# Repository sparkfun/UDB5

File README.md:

UDB5 - UAV Development Board
===============

[  
*UDB5 (GPS-11703)*](https://www.sparkfun.com/products/11703)

The UDB5 is the fith generation UAV Development board. The main difference from UDB4 is that we moved to an MPU-6000 for the accelerometer and gyro.

For information on the codebase see the [gentlenav repository](https://code.google.com/p/gentlenav/) on google code. 

Repository Contents
-------------------

* **/hardware** - Eagle PCB layout files

License Information
-------------------

All contents of this repository are released under [Creative Commons Share-alike 3.0](http://creativecommons.org/licenses/by-sa/3.0/).

Authors: Jordan McConnell, Aaron Weiss @ SparkFun Electonics

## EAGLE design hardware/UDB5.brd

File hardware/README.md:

UDB5
====

These are the Eagle CAD files for the UDB5.

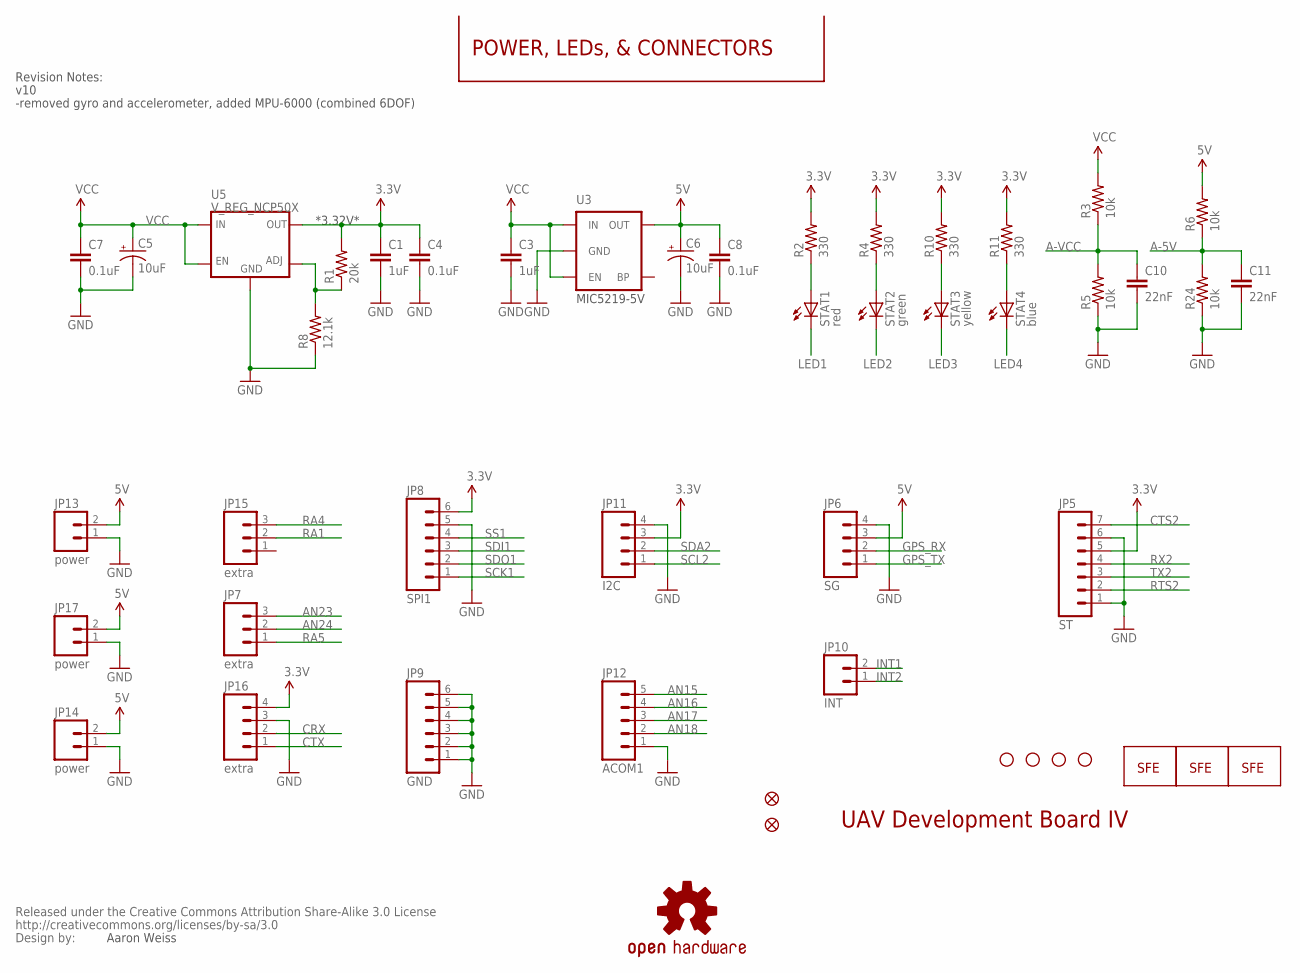
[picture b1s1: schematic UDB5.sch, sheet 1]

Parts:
C1, C3: 1uF; 0402-CAP
C4, C7, C8: 0.1uF; 0402-CAP
C5, C6: 10uF; EIA3216
C10, C11: 22nF; 0402-CAP
CC_TEXT1: CREATIVE_COMMONS
JP3: LOGO-SFENEW; SFE-NEW-WEBLOGO
JP5: ST; 1X07
JP6: SG; 1X04
JP7, JP15: extra; 1X03
JP8: SPI1; 1X06
JP9: GND; 1X06
JP10: INT; 1X02
JP11: I2C; 1X04
JP12: ACOM1; 1X05
JP13, JP14, JP17: power; 1X02
JP16: extra; 1X04
JP18, JP19: FIDUCIAL1X2.5; FIDUCIAL-1X2.5
LOGO1: LOGO-SFENW2; SFE-NEW-WEB
R1: 20k; 0402-RES
R2, R4, R10, R11: 330; 0402-RES
R3, R5, R6, R24: 10k; 0402-RES
R8: 12.1k; 0402-RES
STAT1: red; LED-0603
STAT2: green; LED-0603
STAT3: yellow; LED-0603
STAT4: blue; LED-0603
U3: V_REG_LDOSMD; SOT23-5
U5: V_REG_NCP50X; DPAK-5
U$2, U$3, U$4, U$5: STAND-OFF
U$9: OSHW-LOGOS; OSHW-LOGO-S
U$10: LOGO-SFESK; SFE-LOGO-FLAME

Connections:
3.3V: C1.1, C4.1, JP5.5, JP8.6, JP11.3, JP16.4, R1.2, R2.2, R4.2, R10.2, R11.2, U5.VOUT (OUT); also elsewhere on the board
5V: C6.A (+), C8.1, JP6.3, JP13.2, JP14.2, JP17.2, R6.2, U3.5 (OUT); also elsewhere on the board
A-5V: C11.1, R6.1, R24.2; also elsewhere on the board
A-VCC: C10.1, R3.1, R5.2; also elsewhere on the board
AN15: JP12.5; also elsewhere on the board
AN16: JP12.4; also elsewhere on the board
AN17: JP12.3; also elsewhere on the board
AN18: JP12.2; also elsewhere on the board
AN23: JP7.3; also elsewhere on the board
AN24: JP7.2; also elsewhere on the board
CRX: JP16.2; also elsewhere on the board
CTS2: JP5.7; also elsewhere on the board
CTX: JP16.1; also elsewhere on the board
GND: C1.2, C3.2, C4.2, C5.C (-), C6.C (-), C7.2, C8.2, C10.2, C11.2, JP5.1, JP5.6, JP6.4, JP8.5, JP9.1, JP9.2, JP9.3, JP9.4, JP9.5, JP9.6, JP11.4, JP12.1, JP13.1, JP14.1, JP16.3, JP17.1, R5.1, R8.1, R24.1, U3.2 (GND), U5.GND; also elsewhere on the board
GPS_RX: JP6.2; also elsewhere on the board
GPS_TX: JP6.1; also elsewhere on the board
INT1: JP10.2; also elsewhere on the board
INT2: JP10.1; also elsewhere on the board
LED1: STAT1.C; also elsewhere on the board
LED2: STAT2.C; also elsewhere on the board
LED3: STAT3.C; also elsewhere on the board
LED4: STAT4.C; also elsewhere on the board
unnamed: R2.1, STAT1.A
unnamed: R4.1, STAT2.A
unnamed: R1.1, R8.2, U5.ADJ
unnamed: R10.1, STAT3.A
unnamed: R11.1, STAT4.A
RA1: JP15.2; also elsewhere on the board
RA4: JP15.3; also elsewhere on the board
RA5: JP7.1; also elsewhere on the board
RTS2: JP5.2; also elsewhere on the board
RX2: JP5.4; also elsewhere on the board
SCK1: JP8.1; also elsewhere on the board
SCL2: JP11.1; also elsewhere on the board
SDA2: JP11.2; also elsewhere on the board
SDI1: JP8.3; also elsewhere on the board
SDO1: JP8.2; also elsewhere on the board
SS1: JP8.4; also elsewhere on the board
TX2: JP5.3; also elsewhere on the board
VCC: C3.1, C5.A (+), C7.1, R3.2, U3.1 (IN), U3.3 (EN), U5.EN, U5.VIN (IN); also elsewhere on the board

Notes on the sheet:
Aaron Weiss
POWER, LEDs, & CONNECTORS
UAV Development Board IV
*3.32V*
MIC5219-5V
v10
-removed gyro and accelerometer, added MPU-6000 (combined 6DOF)
Revision Notes:

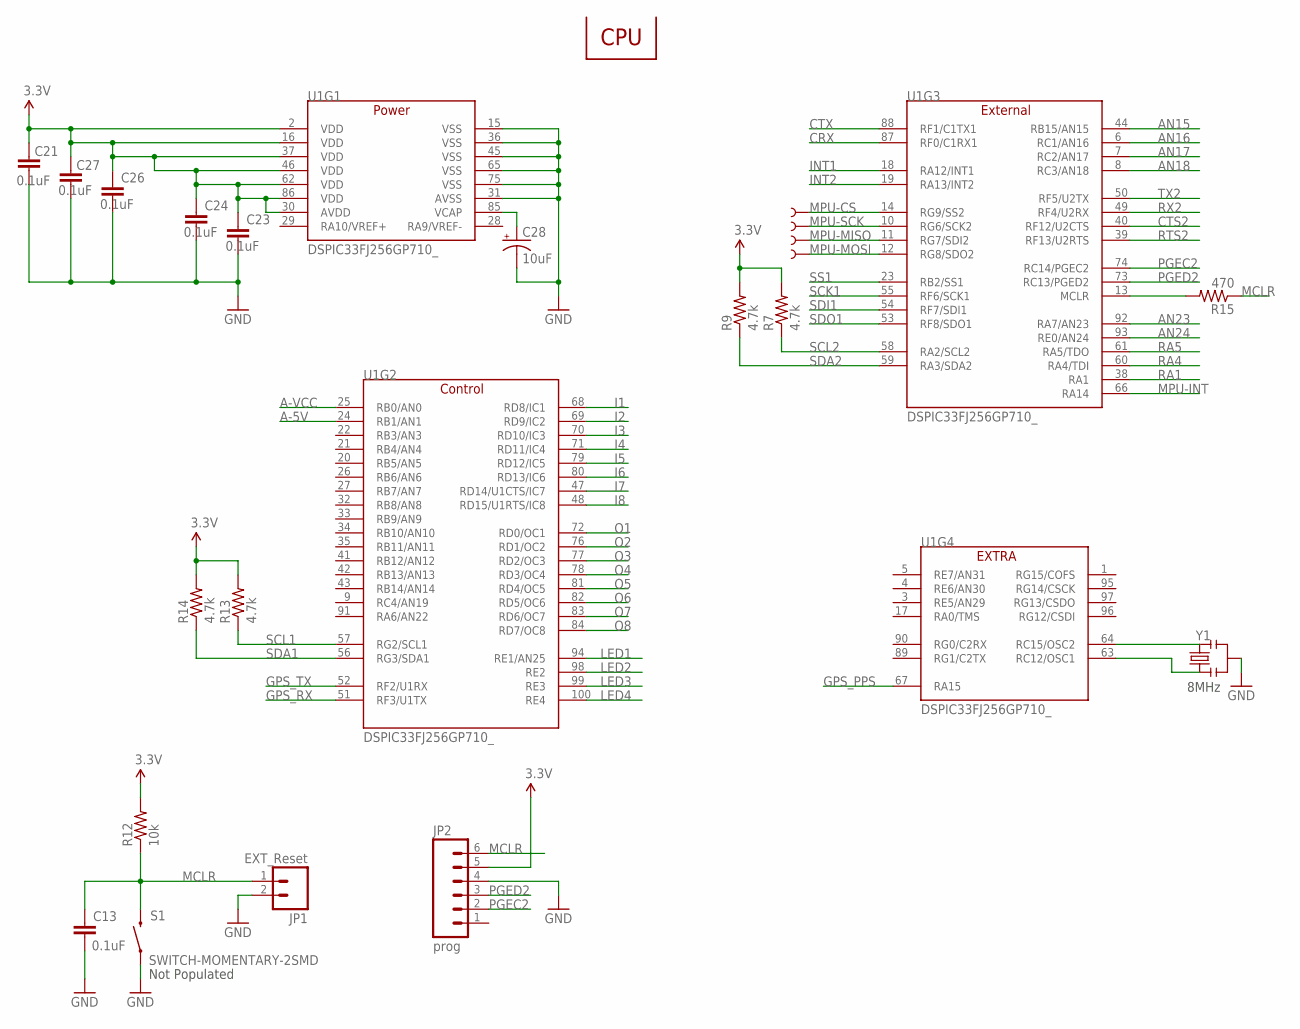
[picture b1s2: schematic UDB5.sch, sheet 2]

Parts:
C13, C21, C23, C24, C26, C27: 0.1uF; 0402-CAP
C28: 10uF; EIA3216
JP1: EXT_Reset; 1X02
JP2: prog; 1X06
R7, R9, R13, R14: 4.7k; 0402-RES
R12: 10k; 0402-RES
R15: 470; 0402-RES
S1: SWITCH-MOMENTARY-2SMD; TACTILE_SWITCH_SMD
TP1, TP2, TP3, TP4: TEST-POINT3; PAD.03X.03
U1: DSPIC33FJ256GP710_; TQFP-100-12X12MM
Y1: RESONATORSMD; RESONATOR-SMD

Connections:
3.3V: C21.1, C23.1, C24.1, C26.1, C27.1, JP2.5, R7.2, R9.2, R12.2, R13.2, R14.2, U1.2 (VDD), U1.16 (VDD), U1.30 (AVDD), U1.37 (VDD), U1.46 (VDD), U1.62 (VDD), U1.86 (VDD); also elsewhere on the board
A-5V: U1.24 (RB1/AN1); also elsewhere on the board
A-VCC: U1.25 (RB0/AN0); also elsewhere on the board
AN15: U1.44 (RB15/AN15); also elsewhere on the board
AN16: U1.6 (RC1/AN16); also elsewhere on the board
AN17: U1.7 (RC2/AN17); also elsewhere on the board
AN18: U1.8 (RC3/AN18); also elsewhere on the board
AN23: U1.92 (RA7/AN23); also elsewhere on the board
AN24: U1.93 (RE0/AN24); also elsewhere on the board
CRX: U1.87 (RF0/C1RX1); also elsewhere on the board
CTS2: U1.40 (RF12/U2CTS); also elsewhere on the board
CTX: U1.88 (RF1/C1TX1); also elsewhere on the board
GND: C13.2, C21.2, C23.2, C24.2, C26.2, C27.2, C28.C (-), JP1.2, JP2.4, S1.1, U1.15 (VSS), U1.31 (AVSS), U1.36 (VSS), U1.45 (VSS), U1.65 (VSS), U1.75 (VSS), Y1.2; also elsewhere on the board
GPS_PPS: U1.67 (RA15); also elsewhere on the board
GPS_RX: U1.51 (RF3/U1TX); also elsewhere on the board
GPS_TX: U1.52 (RF2/U1RX); also elsewhere on the board
I1: U1.68 (RD8/IC1); also elsewhere on the board
I2: U1.69 (RD9/IC2); also elsewhere on the board
I3: U1.70 (RD10/IC3); also elsewhere on the board
I4: U1.71 (RD11/IC4); also elsewhere on the board
I5: U1.79 (RD12/IC5); also elsewhere on the board
I6: U1.80 (RD13/IC6); also elsewhere on the board
I7: U1.47 (RD14/U1CTS/IC7); also elsewhere on the board
I8: U1.48 (RD15/U1RTS/IC8); also elsewhere on the board
INT1: U1.18 (RA12/INT1); also elsewhere on the board
INT2: U1.19 (RA13/INT2); also elsewhere on the board
LED1: U1.94 (RE1/AN25); also elsewhere on the board
LED2: U1.98 (RE2); also elsewhere on the board
LED3: U1.99 (RE3); also elsewhere on the board
LED4: U1.100 (RE4); also elsewhere on the board
MCLR: C13.1, JP1.1, JP2.6, R12.1, R15.1, S1.3 (2)
MPU-CS: TP1.P$1, U1.14 (RG9/SS2); also elsewhere on the board
MPU-INT: U1.66 (RA14); also elsewhere on the board
MPU-MISO: TP3.P$1, U1.11 (RG7/SDI2); also elsewhere on the board
MPU-MOSI: TP4.P$1, U1.12 (RG8/SDO2); also elsewhere on the board
MPU-SCK: TP2.P$1, U1.10 (RG6/SCK2); also elsewhere on the board
unnamed: U1.64 (RC15/OSC2), Y1.3
unnamed: U1.63 (RC12/OSC1), Y1.1
unnamed: R15.2, U1.13 (MCLR)
unnamed: C28.A (+), U1.85 (VCAP)
O1: U1.72 (RD0/OC1); also elsewhere on the board
O2: U1.76 (RD1/OC2); also elsewhere on the board
O3: U1.77 (RD2/OC3); also elsewhere on the board
O4: U1.78 (RD3/OC4); also elsewhere on the board
O5: U1.81 (RD4/OC5); also elsewhere on the board
O6: U1.82 (RD5/OC6); also elsewhere on the board
O7: U1.83 (RD6/OC7); also elsewhere on the board
O8: U1.84 (RD7/OC8); also elsewhere on the board
PGEC2: JP2.2, U1.74 (RC14/PGEC2)
PGED2: JP2.3, U1.73 (RC13/PGED2)
RA1: U1.38 (RA1); also elsewhere on the board
RA4: U1.60 (RA4/TDI); also elsewhere on the board
RA5: U1.61 (RA5/TDO); also elsewhere on the board
RTS2: U1.39 (RF13/U2RTS); also elsewhere on the board
RX2: U1.49 (RF4/U2RX); also elsewhere on the board
SCK1: U1.55 (RF6/SCK1); also elsewhere on the board
SCL1: R13.1, U1.57 (RG2/SCL1); also elsewhere on the board
SCL2: R7.1, U1.58 (RA2/SCL2); also elsewhere on the board
SDA1: R14.1, U1.56 (RG3/SDA1); also elsewhere on the board
SDA2: R9.1, U1.59 (RA3/SDA2); also elsewhere on the board
SDI1: U1.54 (RF7/SDI1); also elsewhere on the board
SDO1: U1.53 (RF8/SDO1); also elsewhere on the board
SS1: U1.23 (RB2/SS1); also elsewhere on the board
TX2: U1.50 (RF5/U2TX); also elsewhere on the board

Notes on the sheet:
CPU
8MHz
Not Populated

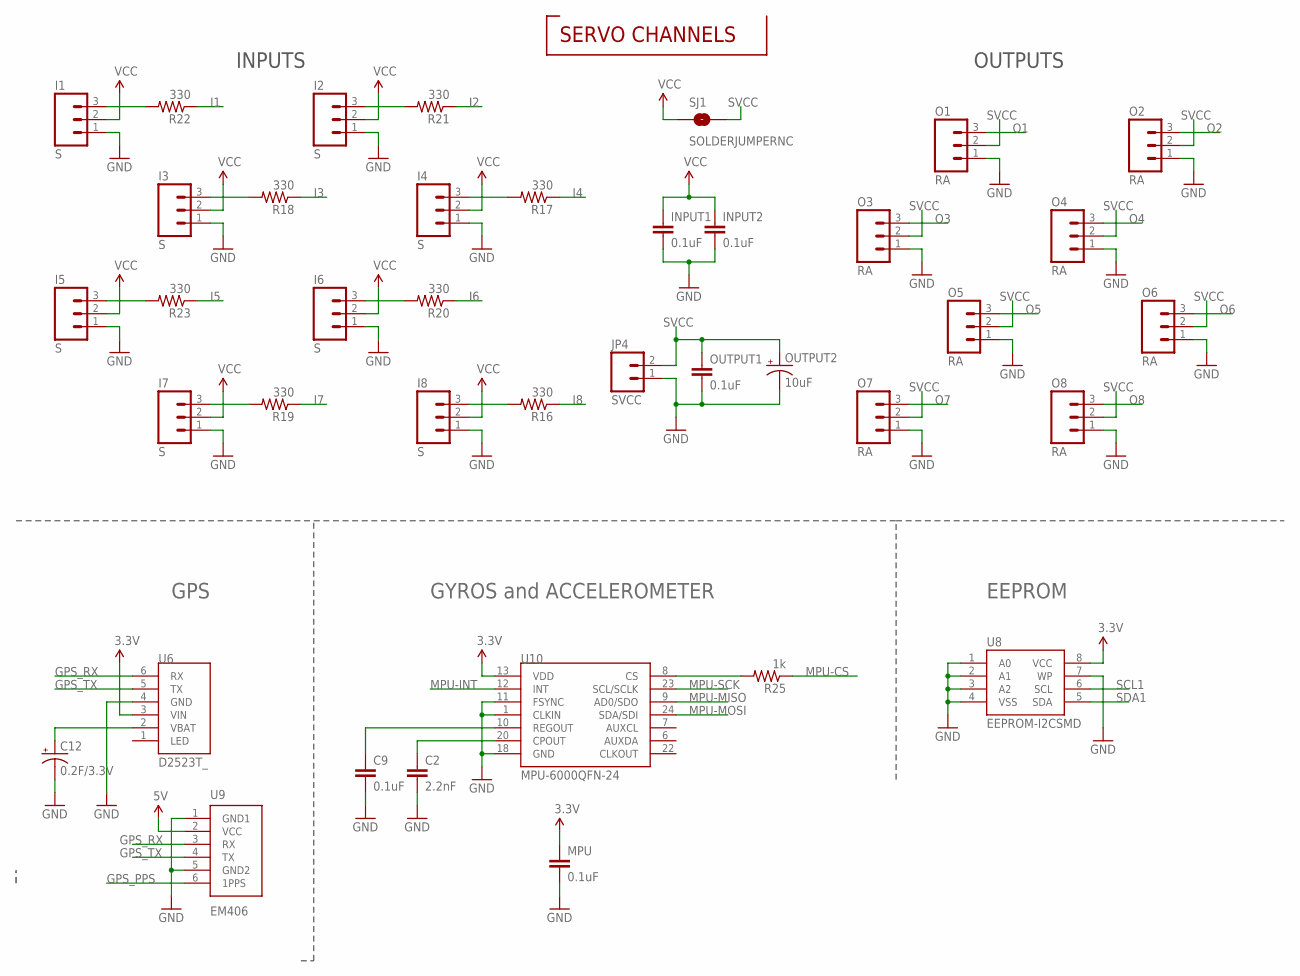
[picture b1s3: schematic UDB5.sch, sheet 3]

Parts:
C2: 2.2nF; 0402-CAP
C9: 0.1uF; 0402-CAP
C12: 0.2F/3.3V; EN_J2
I1, I2, I3, I4, I5, I6, I7, I8: S; 1X03
INPUT1, INPUT2: 0.1uF; 0402-CAP
JP4: SVCC; 1X02
MPU: 0.1uF; 0402-CAP
O1, O2, O3, O4, O5, O6, O7, O8: RA; 1X03
OUTPUT1: 0.1uF; 0402-CAP
OUTPUT2: 10uF; EIA3216
R16, R17, R18, R19, R20, R21, R22, R23: 330; 0402-RES
R25: 1k; 0402-RES
SJ1: SOLDERJUMPERNC; SJ_2S
U6: D2523T_; EM406
U8: EEPROM-I2CSMD; SO08
U9: EM406
U10: MPU-6000QFN-24; QFN-24-TESTING

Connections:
3.3V: MPU.1, U6.3 (VIN), U8.8 (VCC), U10.13 (VDD); also elsewhere on the board
5V: U9.2 (VCC); also elsewhere on the board
GND: C2.2, C9.2, C12.-, I1.1, I2.1, I3.1, I4.1, I5.1, I6.1, I7.1, I8.1, INPUT1.2, INPUT2.2, JP4.1, MPU.2, O1.1, O2.1, O3.1, O4.1, O5.1, O6.1, O7.1, O8.1, OUTPUT1.2, OUTPUT2.C (-), U6.4 (GND), U8.1 (A0), U8.2 (A1), U8.3 (A2), U8.4 (VSS), U8.7 (WP), U9.1 (GND1), U9.5 (GND2), U10.1 (CLKIN), U10.11 (FSYNC), U10.18 (GND); also elsewhere on the board
GPS_PPS: U9.6 (1PPS); also elsewhere on the board
GPS_RX: U6.6 (RX), U9.3 (RX); also elsewhere on the board
GPS_TX: U6.5 (TX), U9.4 (TX); also elsewhere on the board
I1: R22.1; also elsewhere on the board
I2: R21.1; also elsewhere on the board
I3: R18.1; also elsewhere on the board
I4: R17.1; also elsewhere on the board
I5: R23.1; also elsewhere on the board
I6: R20.1; also elsewhere on the board
I7: R19.1; also elsewhere on the board
I8: R16.1; also elsewhere on the board
MPU-CS: R25.1; also elsewhere on the board
MPU-INT: U10.12 (INT); also elsewhere on the board
MPU-MISO: U10.9 (AD0/SDO); also elsewhere on the board
MPU-MOSI: U10.24 (SDA/SDI); also elsewhere on the board
MPU-SCK: U10.23 (SCL/SCLK); also elsewhere on the board
unnamed: C12.+, U6.2 (VBAT)
unnamed: R25.2, U10.8 (CS)
unnamed: C2.1, U10.20 (CPOUT)
unnamed: I8.3, R16.2
unnamed: I4.3, R17.2
unnamed: C9.1, U10.10 (REGOUT)
unnamed: I3.3, R18.2
unnamed: I7.3, R19.2
unnamed: I6.3, R20.2
unnamed: I2.3, R21.2
unnamed: I1.3, R22.2
unnamed: I5.3, R23.2
O1: O1.3; also elsewhere on the board
O2: O2.3; also elsewhere on the board
O3: O3.3; also elsewhere on the board
O4: O4.3; also elsewhere on the board
O5: O5.3; also elsewhere on the board
O6: O6.3; also elsewhere on the board
O7: O7.3; also elsewhere on the board
O8: O8.3; also elsewhere on the board
SCL1: U8.6 (SCL); also elsewhere on the board
SDA1: U8.5 (SDA); also elsewhere on the board
SVCC: JP4.2, O1.2, O2.2, O3.2, O4.2, O5.2, O6.2, O7.2, O8.2, OUTPUT1.1, OUTPUT2.A (+), SJ1.2
VCC: I1.2, I2.2, I3.2, I4.2, I5.2, I6.2, I7.2, I8.2, INPUT1.1, INPUT2.1, SJ1.1; also elsewhere on the board

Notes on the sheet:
INPUTS
OUTPUTS
SERVO CHANNELS
GPS
EEPROM
GYROS and ACCELEROMETER

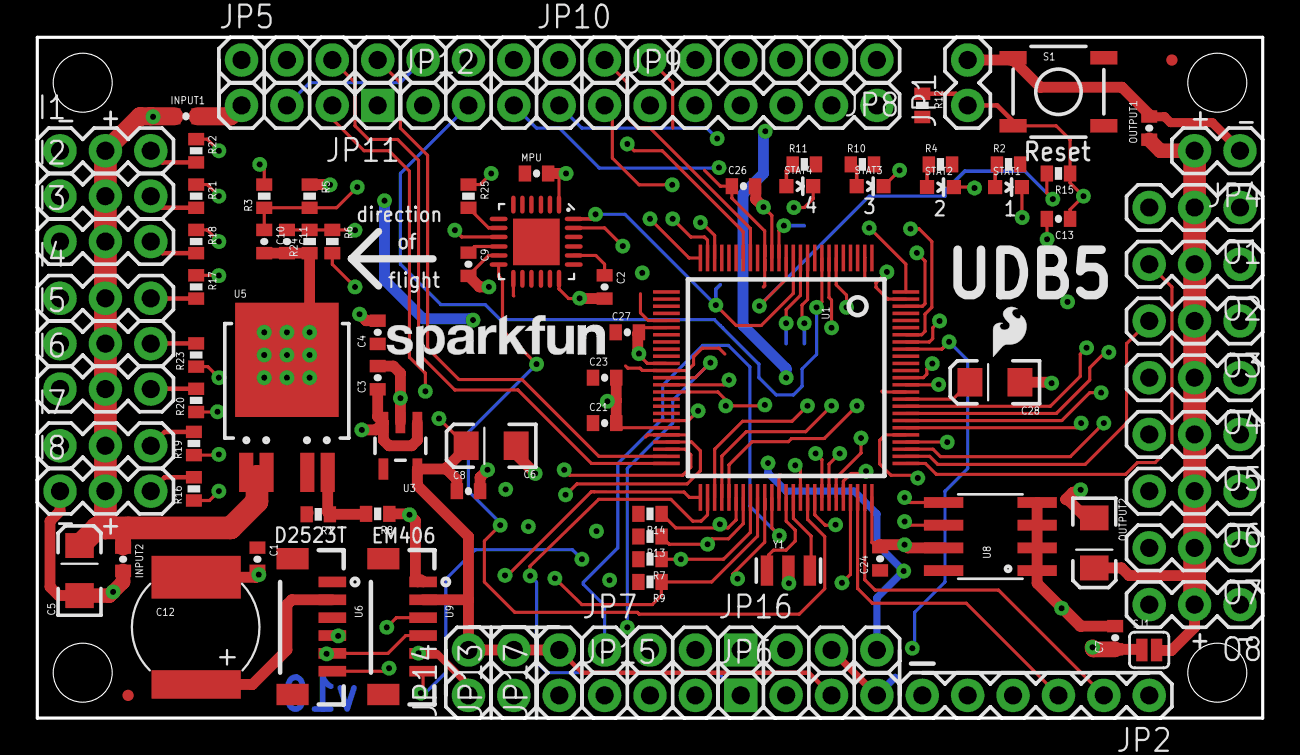
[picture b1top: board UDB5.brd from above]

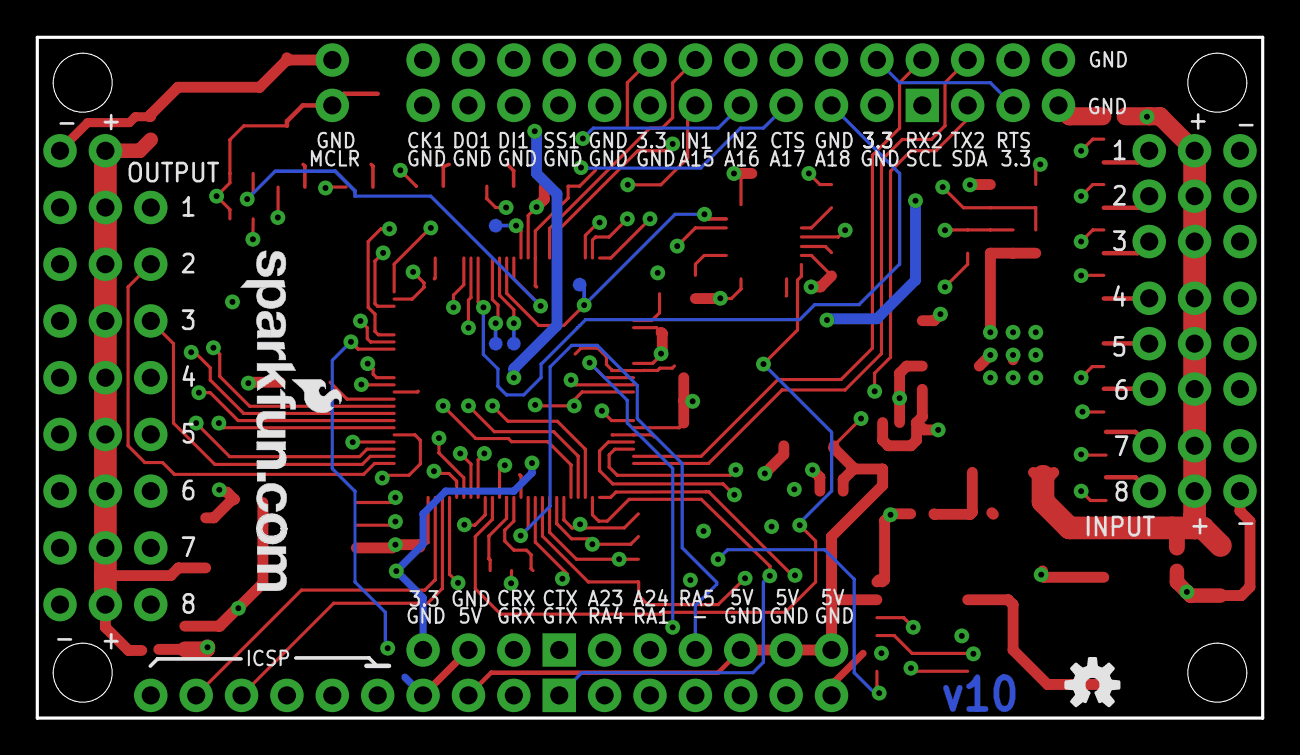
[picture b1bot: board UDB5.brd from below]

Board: 4 copper layers, 68.6 x 38.1 mm, 110 parts (6 on the bottom side), 84 nets.

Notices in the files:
parts and their libraries:
SparkFun-Sensors: Licensing: CC v3.0 Share-Alike You are welcome to use this library for commercial purposes.
SparkFun-Aesthetics: Released under the Creative Commons Attribution Share-Alike 3.0 License
SparkFun-Aesthetics: Creative Commons License summary
